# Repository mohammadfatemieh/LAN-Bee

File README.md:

# LAN-Bee
XBee footprint compatible LAN Module with WIZnet W5500 Ethernet Controller.

* [WIZnet W5500](https://www.wiznet.io/product-item/w5500/) Ethernet Controller (10/100Mbps)
* Integrated IPv4 stack
* SPI interface with 5V tolerant inputs
* XBee compatible Pinout (3.3V)
* Open-Source and released under the [Creative Commons Attribution Share-Alike License](https://creativecommons.org/licenses/by-sa/4.0/).
* **[Documentation on learn.watterott.com](https://learn.watterott.com)**

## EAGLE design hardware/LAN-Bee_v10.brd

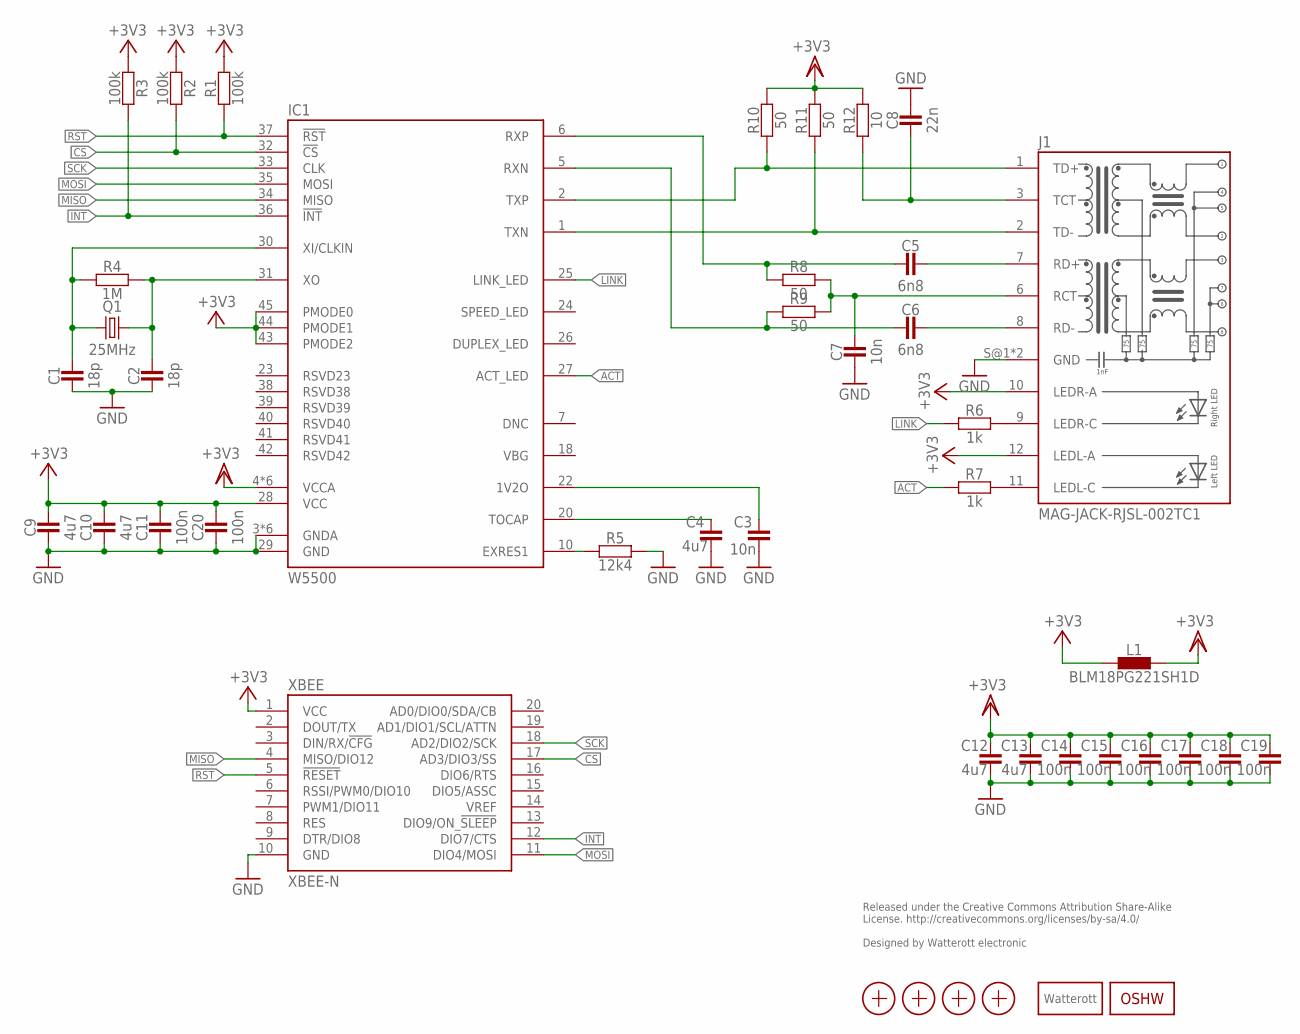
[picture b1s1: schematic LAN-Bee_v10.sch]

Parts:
C1, C2: 18p; C0402
C3, C7: 10n; C0402
C4, C9, C10, C12, C13: 4u7; C0603
C5, C6: 6n8; C0402
C8: 22n; C0402
C11, C14, C15, C16, C17, C18, C19, C20: 100n; C0402
IC1: W5500; TQFP48
J1: MAG-JACK-RJSL-002TC1; RJ45_RJSL-002TC1
L1: BLM18PG221SH1D; C0603
LOGO2: OSHW_LOGOX0070; OSHW_6X70
LOGO3: LOGO_SPARK-2; SPARK_2MM
Q1: 25MHz; CRYSTAL_ZM315
R1, R2, R3: 100k; C0402
R4: 1M; C0402
R5: 12k4; C0402
R6, R7: 1k; C0402
R8, R9, R10, R11: 50; C0402
R12: 10; C0402
X1, X2, X3, X4: PASSER-07; PASSER_07MM
XBEE: XBEE-N; XBEE_N

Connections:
+3V3: C9.2, C10.2, C11.2, C20.2, IC1.28 (VCC), IC1.43 (PMODE2), IC1.44 (PMODE1), IC1.45 (PMODE0), J1.10 (LEDR-A), J1.12 (LEDL-A), L1.1, R1.2, R2.2, R3.2, XBEE.1 (VCC)
ACT: IC1.27 (ACT_LED), R7.2
CS: IC1.32 (!CS), R2.1, XBEE.17 (AD3/DIO3/SS)
GND: C1.1, C2.1, C3.1, C4.1, C7.1, C8.2, C9.1, C10.1, C11.1, C12.1, C13.1, C14.1, C15.1, C16.1, C17.1, C18.1, C19.1, C20.1, IC1.3 (GNDA), IC1.9 (GNDA), IC1.14 (GNDA), IC1.16 (GNDA), IC1.19 (GNDA), IC1.29 (GND), IC1.48 (GNDA), J1.S@1 (GND), J1.S@2 (GND), R5.2, XBEE.10 (GND)
INT: IC1.36 (!INT), R3.1, XBEE.12 (DIO7/CTS)
LEDLC: J1.11 (LEDL-C), R7.1
LEDRC: J1.9 (LEDR-C), R6.1
LINK: IC1.25 (LINK_LED), R6.2
MISO: IC1.34 (MISO), XBEE.4 (MISO/DIO12)
MOSI: IC1.35 (MOSI), XBEE.11 (DIO4/MOSI)
unnamed: IC1.10 (EXRES1), R5.1
unnamed: C3.2, IC1.22 (1V2O)
unnamed: C4.2, IC1.20 (TOCAP)
unnamed: C2.2, IC1.31 (XO), Q1.2, R4.2
unnamed: C1.2, IC1.30 (XI/CLKIN), Q1.1, R4.1
unnamed: C7.2, J1.6 (RCT), R8.1, R9.1
unnamed: C8.1, J1.3 (TCT), R12.2
RD+: C5.2, J1.7 (RD+)
RD-: C6.2, J1.8 (RD-)
RST: IC1.37 (!RST), R1.1, XBEE.5 (!RESET!)
RXN: C6.1, IC1.5 (RXN), R9.2
RXP: C5.1, IC1.6 (RXP), R8.2
SCK: IC1.33 (CLK), XBEE.18 (AD2/DIO2/SCK)
TD+: IC1.2 (TXP), J1.1 (TD+), R10.2
TD-: IC1.1 (TXN), J1.2 (TD-), R11.2
VDD: C12.2, C13.2, C14.2, C15.2, C16.2, C17.2, C18.2, C19.2, IC1.4 (VCCA), IC1.8 (VCCA), IC1.11 (VCCA), IC1.15 (VCCA), IC1.17 (VCCA), IC1.21 (VCCA), L1.2, R10.1, R11.1, R12.1

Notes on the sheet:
Released under the Creative Commons Attribution Share-Alike License. http://creativecommons.org/licenses/by-sa/4.0/ Designed by Watterott electronic

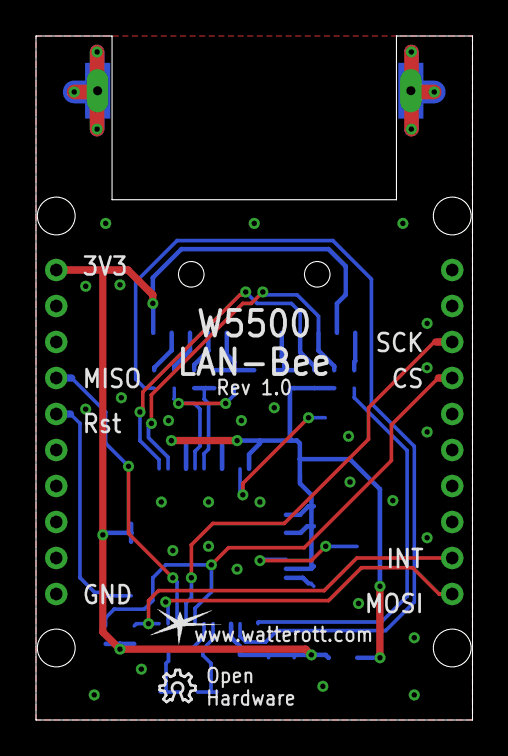
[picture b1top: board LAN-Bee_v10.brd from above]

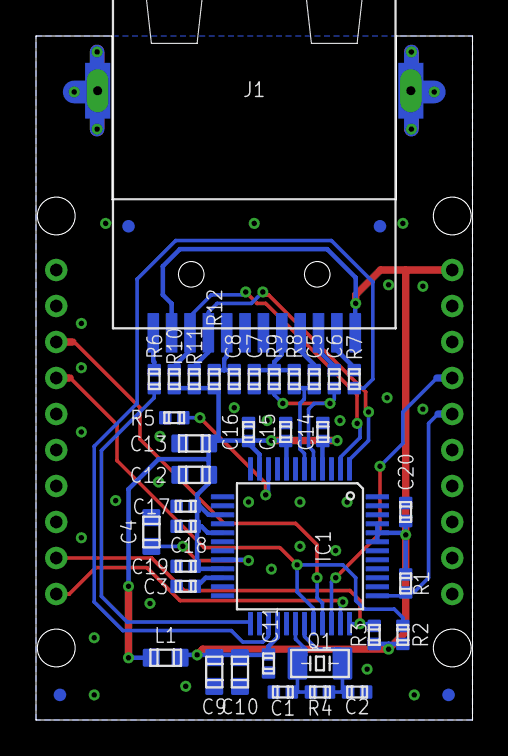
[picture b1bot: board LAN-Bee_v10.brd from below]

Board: 2 copper layers, 24.2 x 38.0 mm, 43 parts (40 on the bottom side), 26 nets.

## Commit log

2018-04-09 added readme
2018-05-03 added layout and schematics
2019-05-14 added picture
